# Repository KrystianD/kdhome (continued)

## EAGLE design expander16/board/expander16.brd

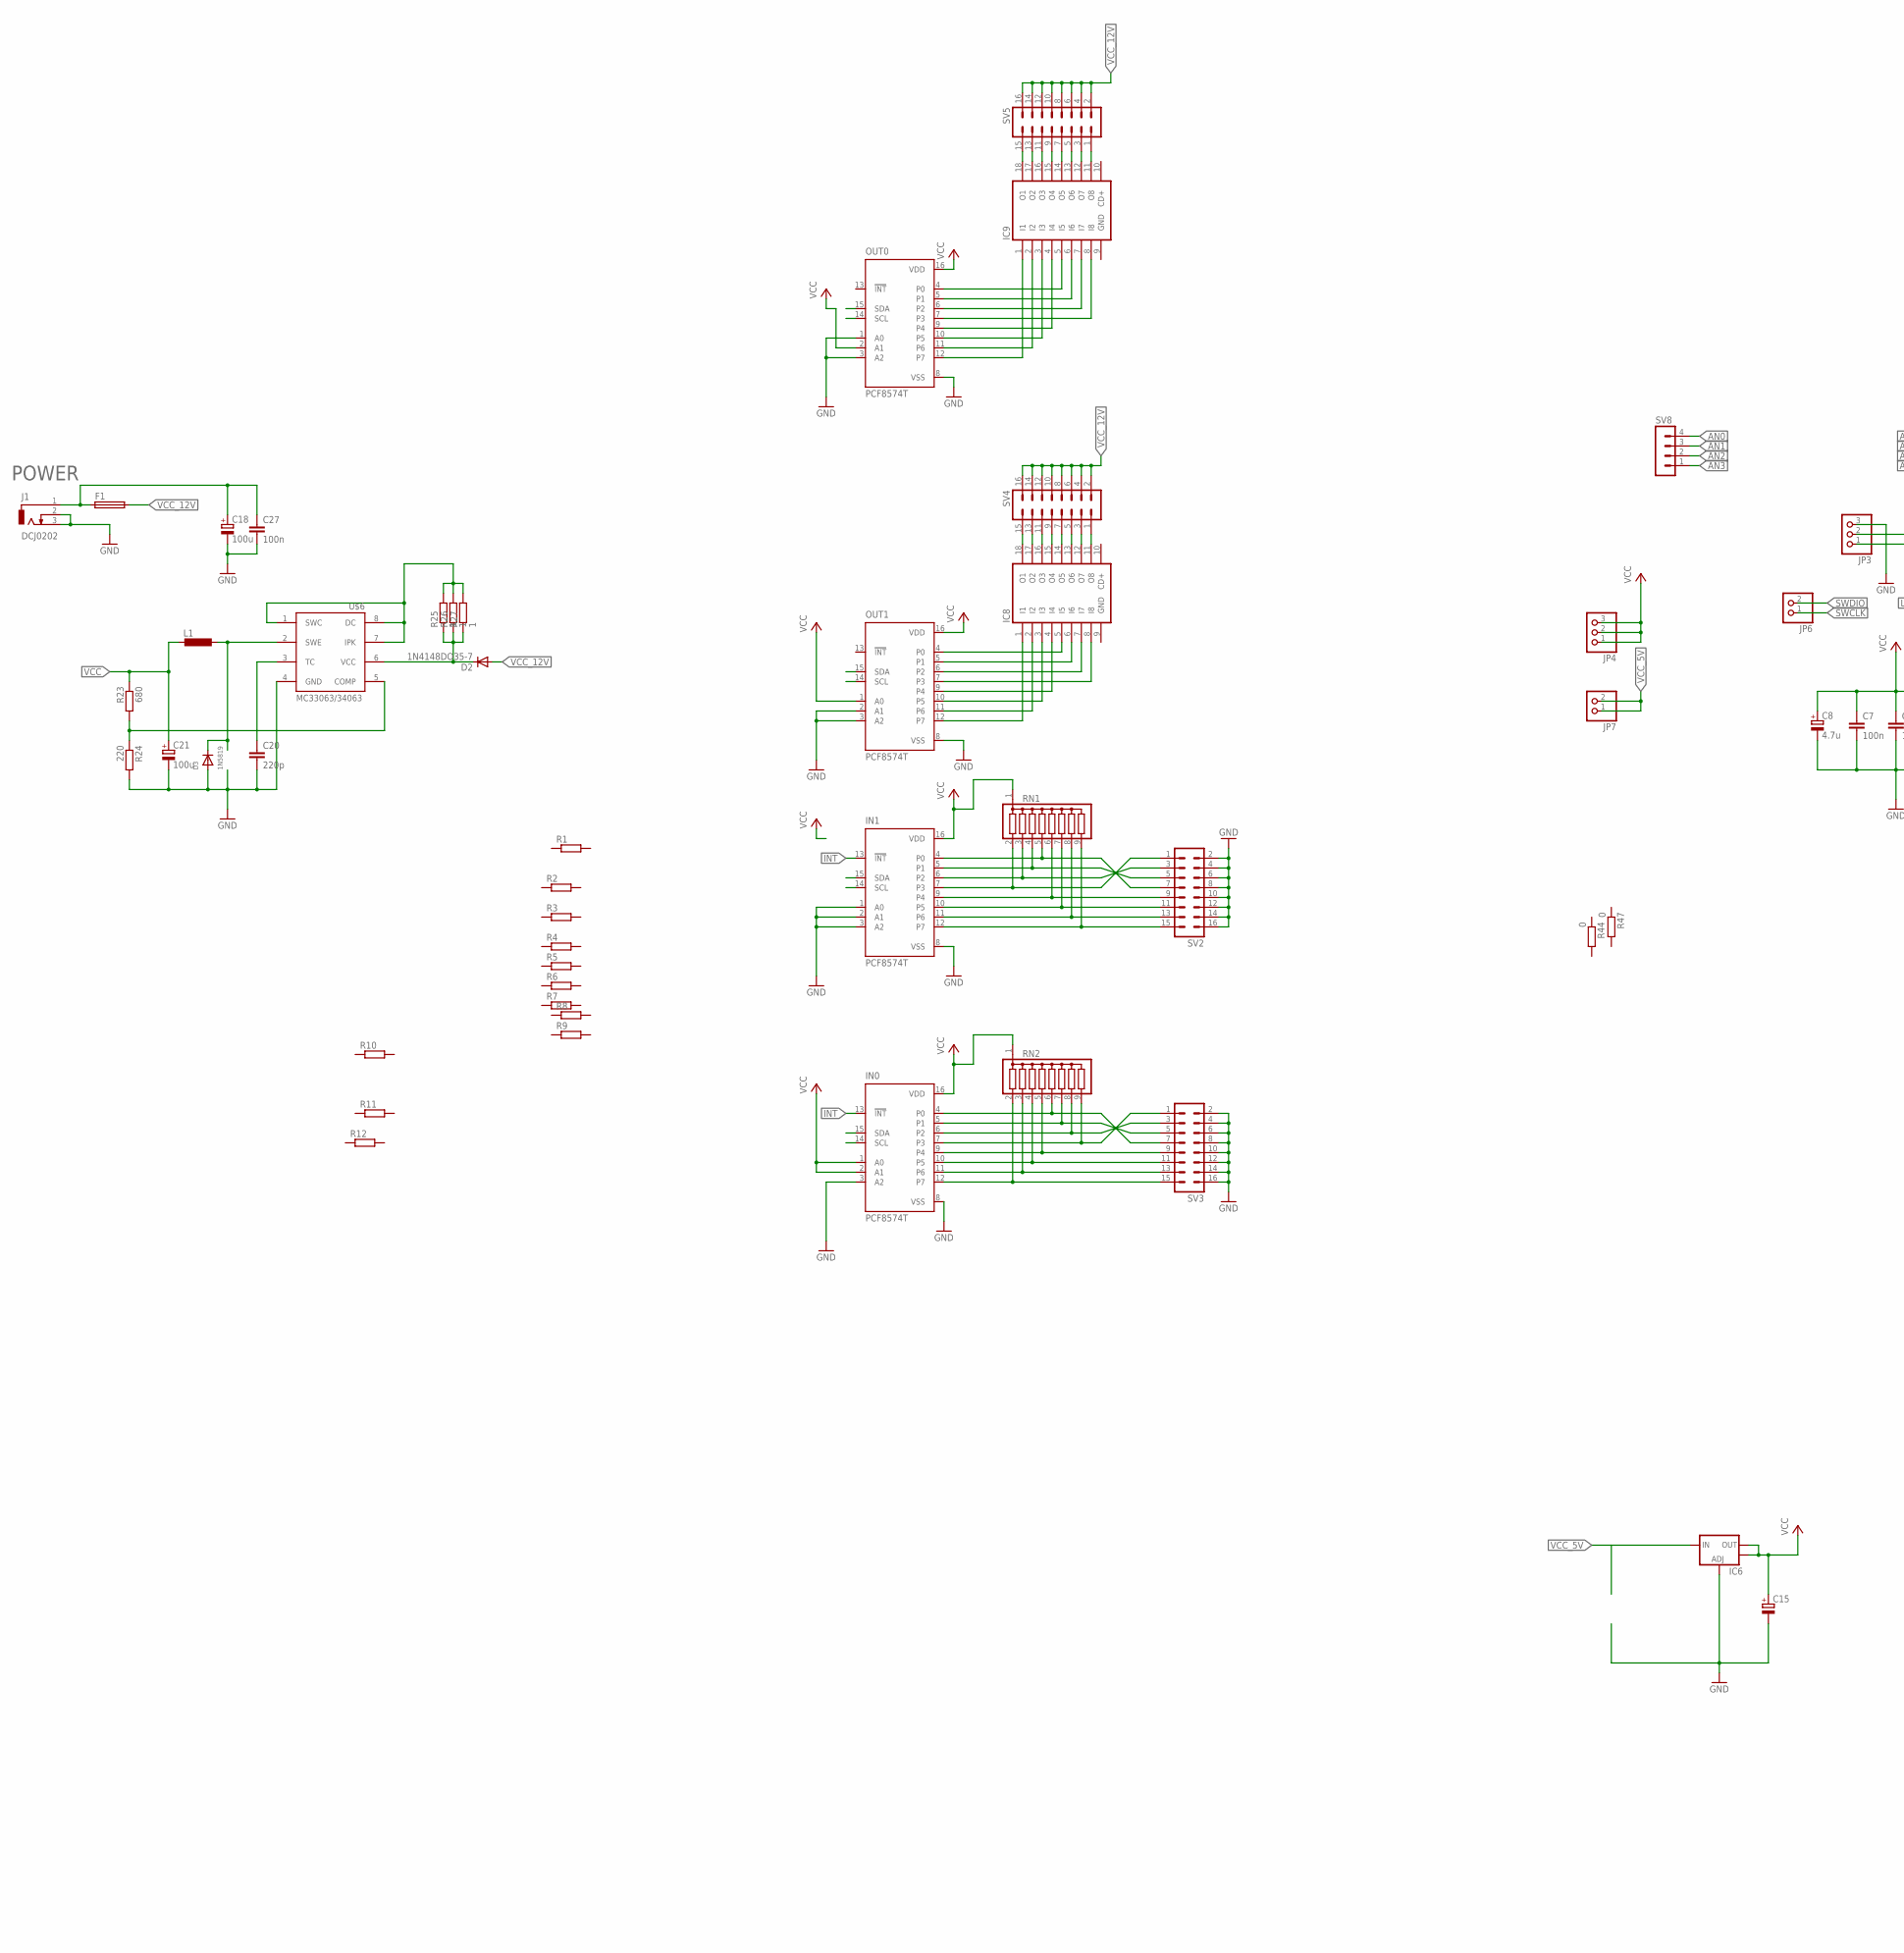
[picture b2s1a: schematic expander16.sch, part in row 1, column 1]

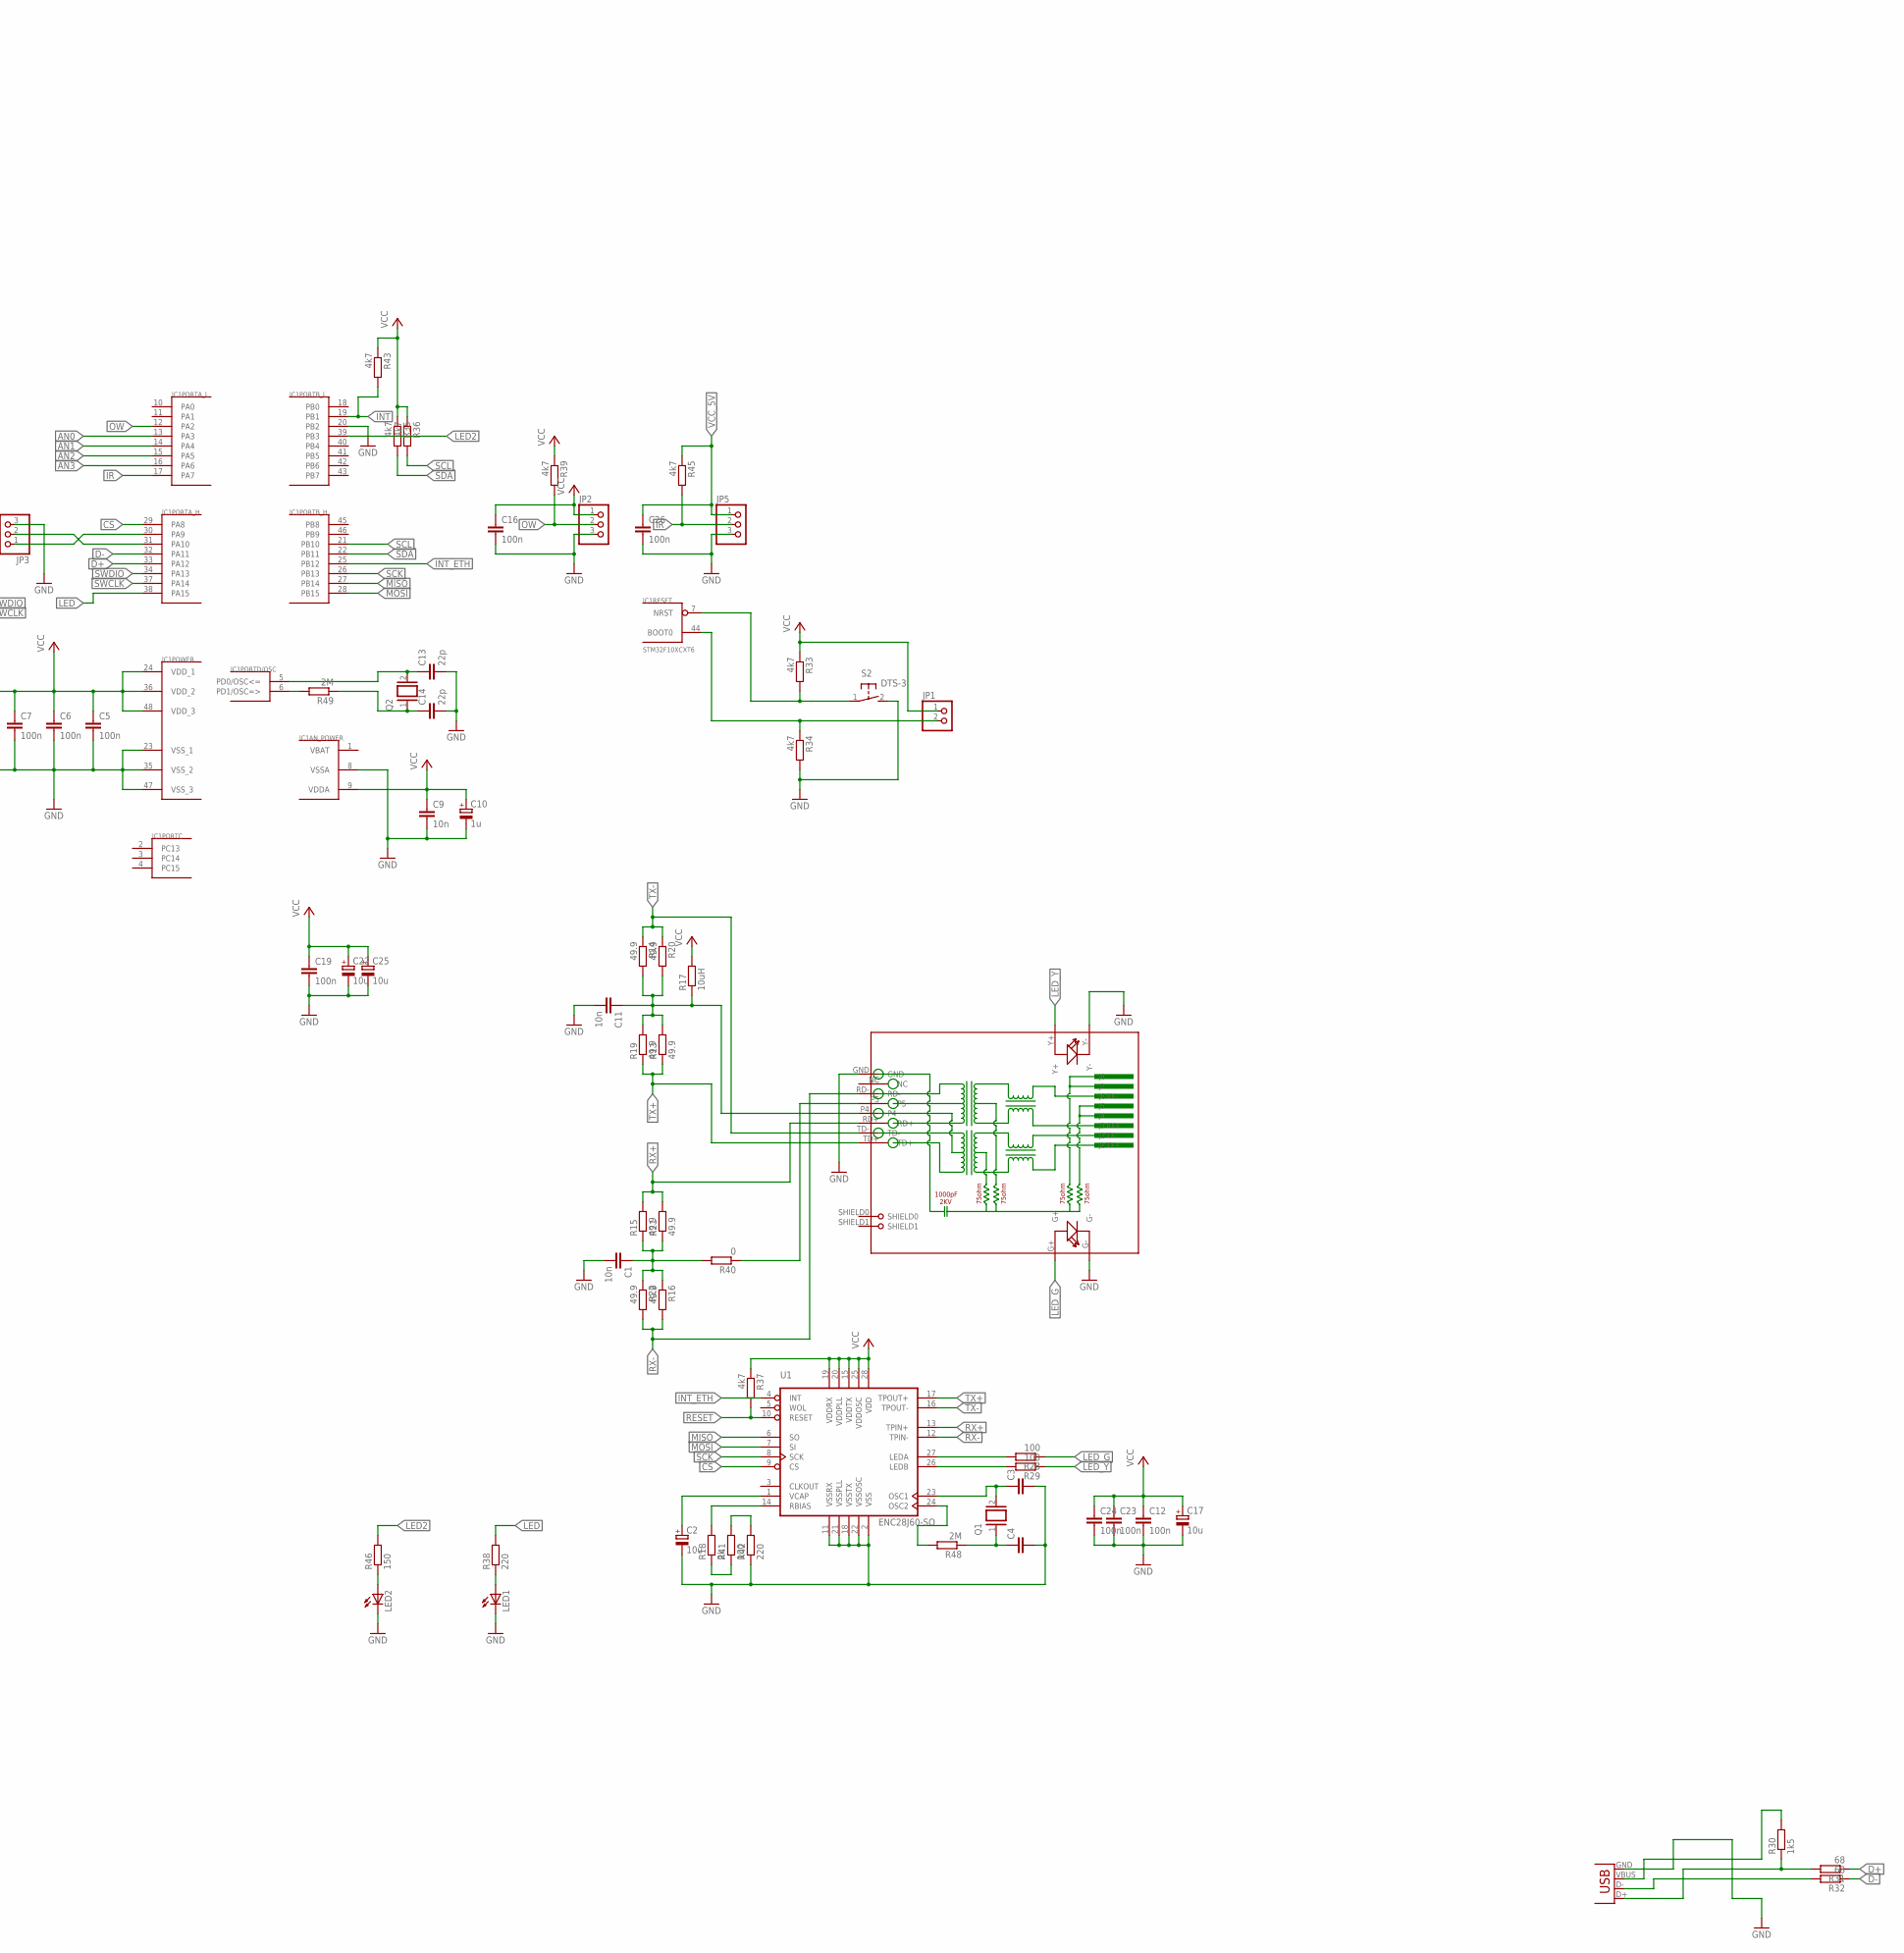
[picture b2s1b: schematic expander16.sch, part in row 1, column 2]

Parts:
C1, C9: 10n; C0805
C2: 10u; B/3528-21W
C3, C4: C-EUC0805; C0805
C5, C6, C7, C12, C19, C23, C24, C27: 100n; C0805
C8: 4.7u; 153CLV-0505
C10: 1u; 153CLV-0505
C11: 10n; C1206
C13, C14: 22p; C0805
C15: CPOL-EUA/3216-18R; A/3216-18R
C16, C26: 100n; C1206
C17, C22, C25: 10u; E1,8-4
C18: 100u; E2,5-7
C20: 220p; C0805
C21: 100u; E3,5-8
D2: 1N4148DO35-7; DO35-7
D3: 1N5819; SMADIODE
F1: SHK20L
IC1: STM32F10XCXT6; TQFP48
IC6: V_REG_LM1117SOT223; SOT223
IC8, IC9: ULN2803AD; SO18W
IN0, IN1: PCF8574T; SO16W
J1: DCJ0202
JP1, JP6, JP7: PINHD-1X2; 1X02
JP2, JP3, JP4, JP5: PINHD-1X3; 1X03
L1: L-EU0207/5V; 0207/5V
LED1: LEDCHIPLED_0805; CHIPLED_0805
LED2: LED3MM
OUT0, OUT1: PCF8574T; SO16W
Q1, Q2: XTAL/S; QS
R1, R2, R3, R4, R5, R6, R7, R8, R9, R10, R11, R12: R-EU_R1206; R1206
R13, R15, R19, R21: 49.9; R1206
R14, R16, R20, R22: 49.9; R0805
R17: 10uH; 0204/5
R18: 2k; R0805
R23: 680; M1206
R24: 220; M1206
R25, R26, R27: 1; R0805
R28, R29: 100; R1206
R30: 1k5; M0805
R31, R32: 68; M1206
R33, R34, R35, R37, R39, R43, R45: 4k7; R0805
R36: 4k7; R1206
R38, R42: 220; R0805
R40: 0; R0805
R41: 100; R0805
R44, R47: 0; R1206
R46: 150; R0805
R48, R49: 2M; R0805
RJ1: HR911105A
RN1, RN2: G08R; SIL9
S2: DTS-3
SV2, SV3, SV4, SV5: MA08-2W
SV8: MA04-1
U1: ENC28J60-SO; SO28W
U$6: MC33063/MC34063D; SO08
X1: USBPTH; USB-B-PTH

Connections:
AN0: IC1.13 (PA3), SV8.4
AN1: IC1.14 (PA4), SV8.3
AN2: IC1.15 (PA5), SV8.2
AN3: IC1.16 (PA6), SV8.1
COMP: R23.2, R24.1, U$6.5 (COMP)
CS: IC1.29 (PA8), U1.9 (CS)
D+: IC1.33 (PA12), R31.1
D-: IC1.32 (PA11), R32.1
GND: C1.2, C2.-, C3.2, C4.2, C5.2, C6.2, C7.2, C8.-, C9.2, C10.-, C11.2, C12.2, C13.2, C14.2, C15.-, C16.2, C17.-, C18.-, C19.2, C20.2, C21.-, C22.-, C23.2, C24.2, C25.-, C26.2, C27.2, D3.A, IC1.8 (VSSA), IC1.20 (PB2), IC1.23 (VSS_1), IC1.35 (VSS_2), IC1.47 (VSS_3), IC6.1 (ADJ), IC8.9 (GND), IC9.9 (GND), IN0.3 (A2), IN0.8 (VSS), IN1.1 (A0), IN1.2 (A1), IN1.3 (A2), IN1.8 (VSS), J1.2, J1.3, JP2.3, JP3.3, JP5.3, LED1.C, LED2.K (C), OUT0.1 (A0), OUT0.3 (A2), OUT0.8 (VSS), OUT1.2 (A1), OUT1.3 (A2), OUT1.8 (VSS), R24.2, R34.2, R42.1, RJ1.G-, RJ1.GND, RJ1.Y-, S2.2, SV2.2, SV2.4, SV2.6, SV2.8, SV2.10, SV2.12, SV2.14, SV2.16, SV3.2, SV3.4, SV3.6, SV3.8, SV3.10, SV3.12, SV3.14, SV3.16, U1.2 (VSS), U1.11 (VSSRX), U1.18 (VSSTX), U1.21 (VSSPLL), U1.22 (VSSOSC), U$6.4 (GND), X1.GND
INT: IC1.19 (PB1), IN0.13 (!INT), IN1.13 (!INT), R43.2
INT_ETH: IC1.25 (PB12), U1.4 (INT)
IPK: R25.2, R26.2, R27.2, U$6.1 (SWC), U$6.7 (IPK), U$6.8 (DC)
IR: IC1.17 (PA7), JP5.2, R45.2
LED: IC1.38 (PA15), R38.2
LED2: IC1.39 (PB3), R46.2
LED_G: R28.1, RJ1.G+
LED_Y: R29.1, RJ1.Y+
MISO: IC1.27 (PB14), U1.6 (SO)
MOSI: IC1.28 (PB15), U1.7 (SI)
unnamed: IC8.18 (O1), SV4.15
unnamed: IN1.5 (P1), RN1.4, SV2.5
unnamed: IN1.6 (P2), RN1.3, SV2.3
unnamed: IN1.7 (P3), RN1.2, SV2.1
unnamed: IN1.11 (P6), RN1.8, SV2.13
unnamed: IN1.12 (P7), RN1.9, SV2.15
unnamed: IN1.10 (P5), RN1.7, SV2.11
unnamed: IN1.9 (P4), RN1.6, SV2.9
unnamed: IN0.12 (P7), RN2.2, SV3.15
unnamed: IN0.11 (P6), RN2.3, SV3.13
unnamed: IN0.10 (P5), RN2.4, SV3.11
unnamed: IN0.9 (P4), RN2.5, SV3.9
unnamed: IN0.7 (P3), RN2.9, SV3.1
unnamed: IN1.4 (P0), RN1.5, SV2.7
unnamed: IC8.17 (O2), SV4.13
unnamed: IN0.4 (P0), RN2.6, SV3.7
unnamed: IC8.5 (I5), OUT1.4 (P0)
unnamed: IC8.6 (I6), OUT1.5 (P1)
unnamed: IC8.7 (I7), OUT1.6 (P2)
unnamed: IC8.8 (I8), OUT1.7 (P3)
unnamed: IC8.4 (I4), OUT1.9 (P4)
unnamed: IC8.3 (I3), OUT1.10 (P5)
unnamed: IC8.2 (I2), OUT1.11 (P6)
unnamed: IC8.1 (I1), OUT1.12 (P7)
unnamed: IC8.16 (O3), SV4.11
unnamed: IN0.5 (P1), RN2.7, SV3.5
unnamed: IN0.6 (P2), RN2.8, SV3.3
unnamed: IC8.15 (O4), SV4.9
unnamed: IC8.14 (O5), SV4.7
unnamed: IC8.13 (O6), SV4.5
unnamed: IC8.12 (O7), SV4.3
unnamed: IC8.11 (O8), SV4.1
unnamed: IC9.1 (I1), OUT0.12 (P7)
unnamed: IC9.2 (I2), OUT0.11 (P6)
unnamed: IC9.3 (I3), OUT0.10 (P5)
unnamed: IC9.4 (I4), OUT0.9 (P4)
unnamed: IC9.8 (I8), OUT0.7 (P3)
unnamed: IC9.7 (I7), OUT0.6 (P2)
unnamed: IC9.6 (I6), OUT0.5 (P1)
unnamed: IC9.5 (I5), OUT0.4 (P0)
unnamed: IC9.11 (O8), SV5.1
unnamed: IC9.12 (O7), SV5.3
unnamed: IC9.13 (O6), SV5.5
unnamed: IC9.14 (O5), SV5.7
unnamed: IC9.15 (O4), SV5.9
unnamed: IC9.16 (O3), SV5.11
unnamed: IC9.17 (O2), SV5.13
unnamed: IC9.18 (O1), SV5.15
unnamed: C11.1, R13.2, R14.2, R17.1, R19.2, R20.2, RJ1.P4
unnamed: R18.2, U1.14 (RBIAS)
unnamed: D3.C, L1.1, U$6.2 (SWE)
unnamed: C2.+, U1.1 (VCAP)
unnamed: C3.1, Q1.2, U1.23 (OSC1)
unnamed: R28.2, U1.27 (LEDA)
unnamed: R48.2, U1.24 (OSC2)
unnamed: C20.1, U$6.3 (TC)
unnamed: C18.+, C27.1, F1.1A, J1.1
unnamed: R29.2, U1.26 (LEDB)
unnamed: R30.1, R31.2, X1.D+
unnamed: R32.2, X1.D-
unnamed: C13.1, IC1.5 (PD0/OSC<=), Q2.2
unnamed: C14.1, Q2.1, R49.1
unnamed: R40.1, RJ1.P5
unnamed: IC1.44 (BOOT0), JP1.2, R34.1
unnamed: LED1.A, R38.1
unnamed: C1.1, R15.1, R16.1, R21.1, R22.1, R40.2
unnamed: R18.1, R41.1
unnamed: R41.2, R42.2
unnamed: LED2.A, R46.1
unnamed: IC1.6 (PD1/OSC=>), R49.2
unnamed: C4.1, Q1.1, R48.1
OW: IC1.12 (PA2), JP2.2, R39.2
RESET: R37.2, U1.10 (RESET)
RST1: IC1.7 (NRST), R33.2, S2.1
RX: IC1.31 (PA10), JP3.2
RX+: R15.2, R21.2, RJ1.RD+, U1.13 (TPIN+)
RX-: R16.2, R22.2, RJ1.RD-, U1.12 (TPIN-)
SCK: IC1.26 (PB13), U1.8 (SCK)
SCL: IC1.21 (PB10), IN0.14 (SCL), IN1.14 (SCL), OUT0.14 (SCL), OUT1.14 (SCL), R36.2
SDA: IC1.22 (PB11), IN0.15 (SDA), IN1.15 (SDA), OUT0.15 (SDA), OUT1.15 (SDA), R35.2
SWCLK: IC1.37 (PA14), JP6.1
SWDIO: IC1.34 (PA13), JP6.2
TX: IC1.30 (PA9), JP3.1
TX+: R13.1, R19.1, RJ1.TD+, U1.17 (TPOUT+)
TX-: R14.1, R20.1, RJ1.TD-, U1.16 (TPOUT-)
VBAT: IC1.1 (VBAT)
VBUS: R30.2, X1.VBUS
VCC: C5.1, C6.1, C7.1, C8.+, C9.1, C10.+, C12.1, C15.+, C16.1, C17.+, C19.1, C21.+, C22.+, C23.1, C24.1, C25.+, IC1.9 (VDDA), IC1.24 (VDD_1), IC1.36 (VDD_2), IC1.48 (VDD_3), IC6.2 (OUT), IC6.4 (OUT), IN0.1 (A0), IN0.2 (A1), IN0.16 (VDD), IN1.16 (VDD), JP1.1, JP2.1, JP4.1, JP4.2, JP4.3, L1.2, OUT0.2 (A1), OUT0.16 (VDD), OUT1.1 (A0), OUT1.16 (VDD), R17.2, R23.1, R33.1, R35.1, R36.1, R37.1, R39.1, R43.1, RN1.1, RN2.1, U1.15 (VDDTX), U1.19 (VDDRX), U1.20 (VDDPLL), U1.25 (VDDOSC), U1.28 (VDD)
VCC_5V: C26.1, IC6.3 (IN), JP5.1, JP7.1, JP7.2, R45.1
VCC_12V: D2.A, F1.2A, SV4.2, SV4.4, SV4.6, SV4.8, SV4.10, SV4.12, SV4.14, SV4.16, SV5.2, SV5.4, SV5.6, SV5.8, SV5.10, SV5.12, SV5.14, SV5.16
VCC_12V_D: D2.C, R25.1, R26.1, R27.1, U$6.6 (VCC)

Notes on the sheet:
POWER

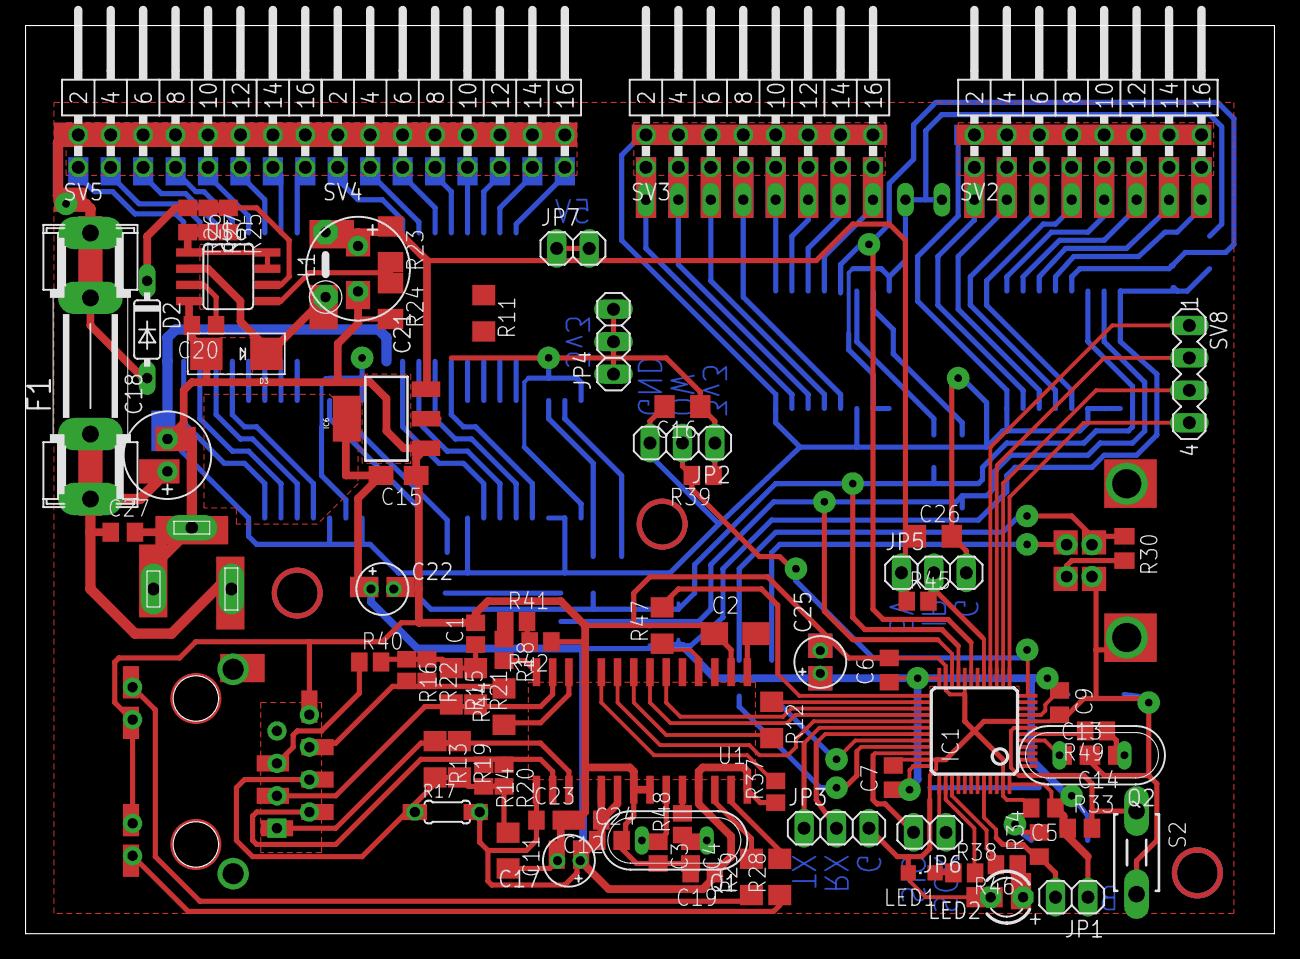
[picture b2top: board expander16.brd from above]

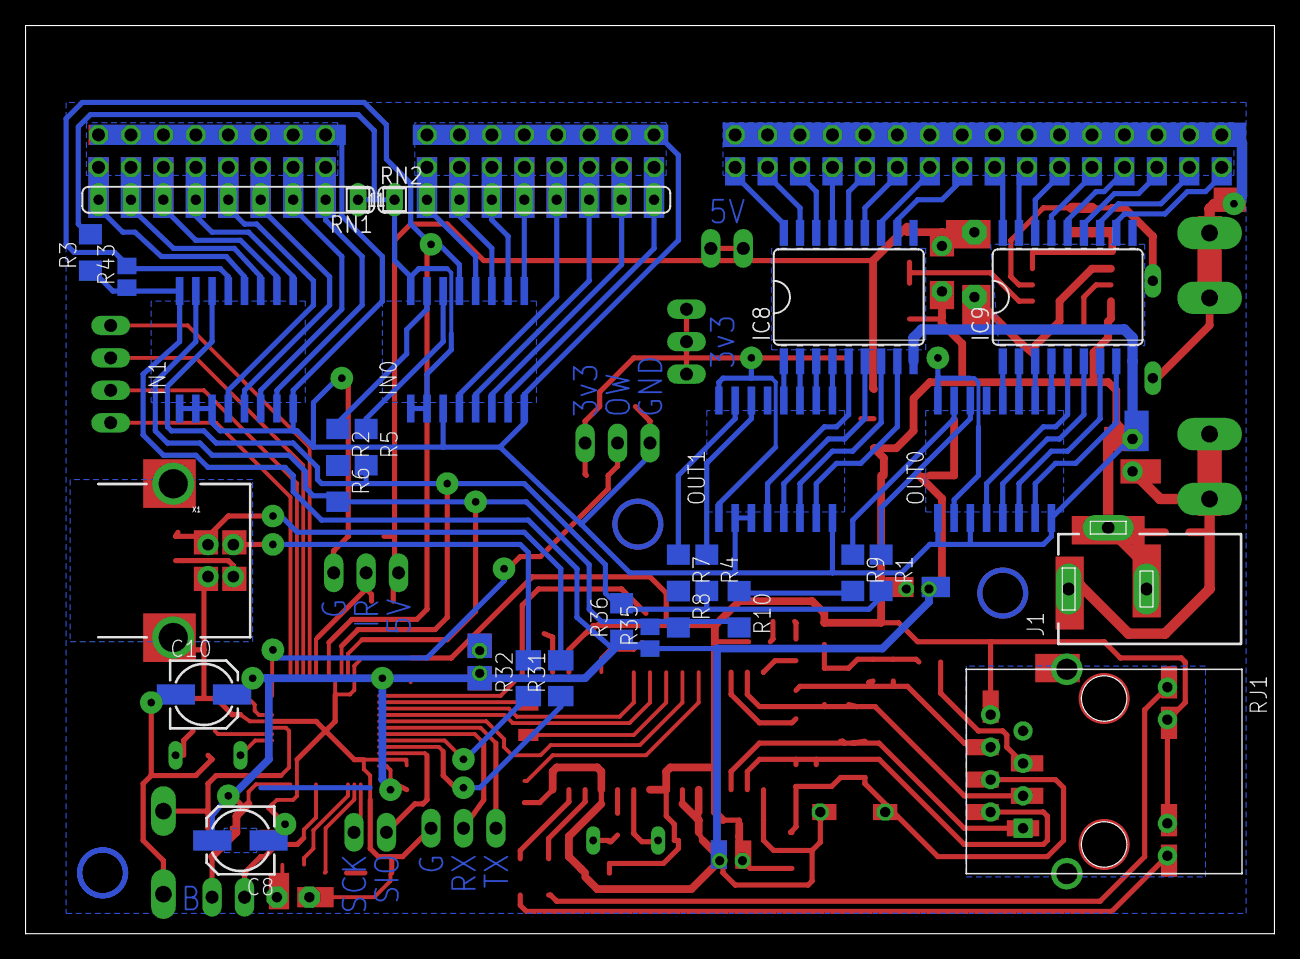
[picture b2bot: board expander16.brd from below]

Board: 2 copper layers, 97.8 x 71.1 mm, 112 parts (28 on the bottom side), 109 nets.
